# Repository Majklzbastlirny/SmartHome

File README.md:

# SmartHome
My smarthome ecosystem

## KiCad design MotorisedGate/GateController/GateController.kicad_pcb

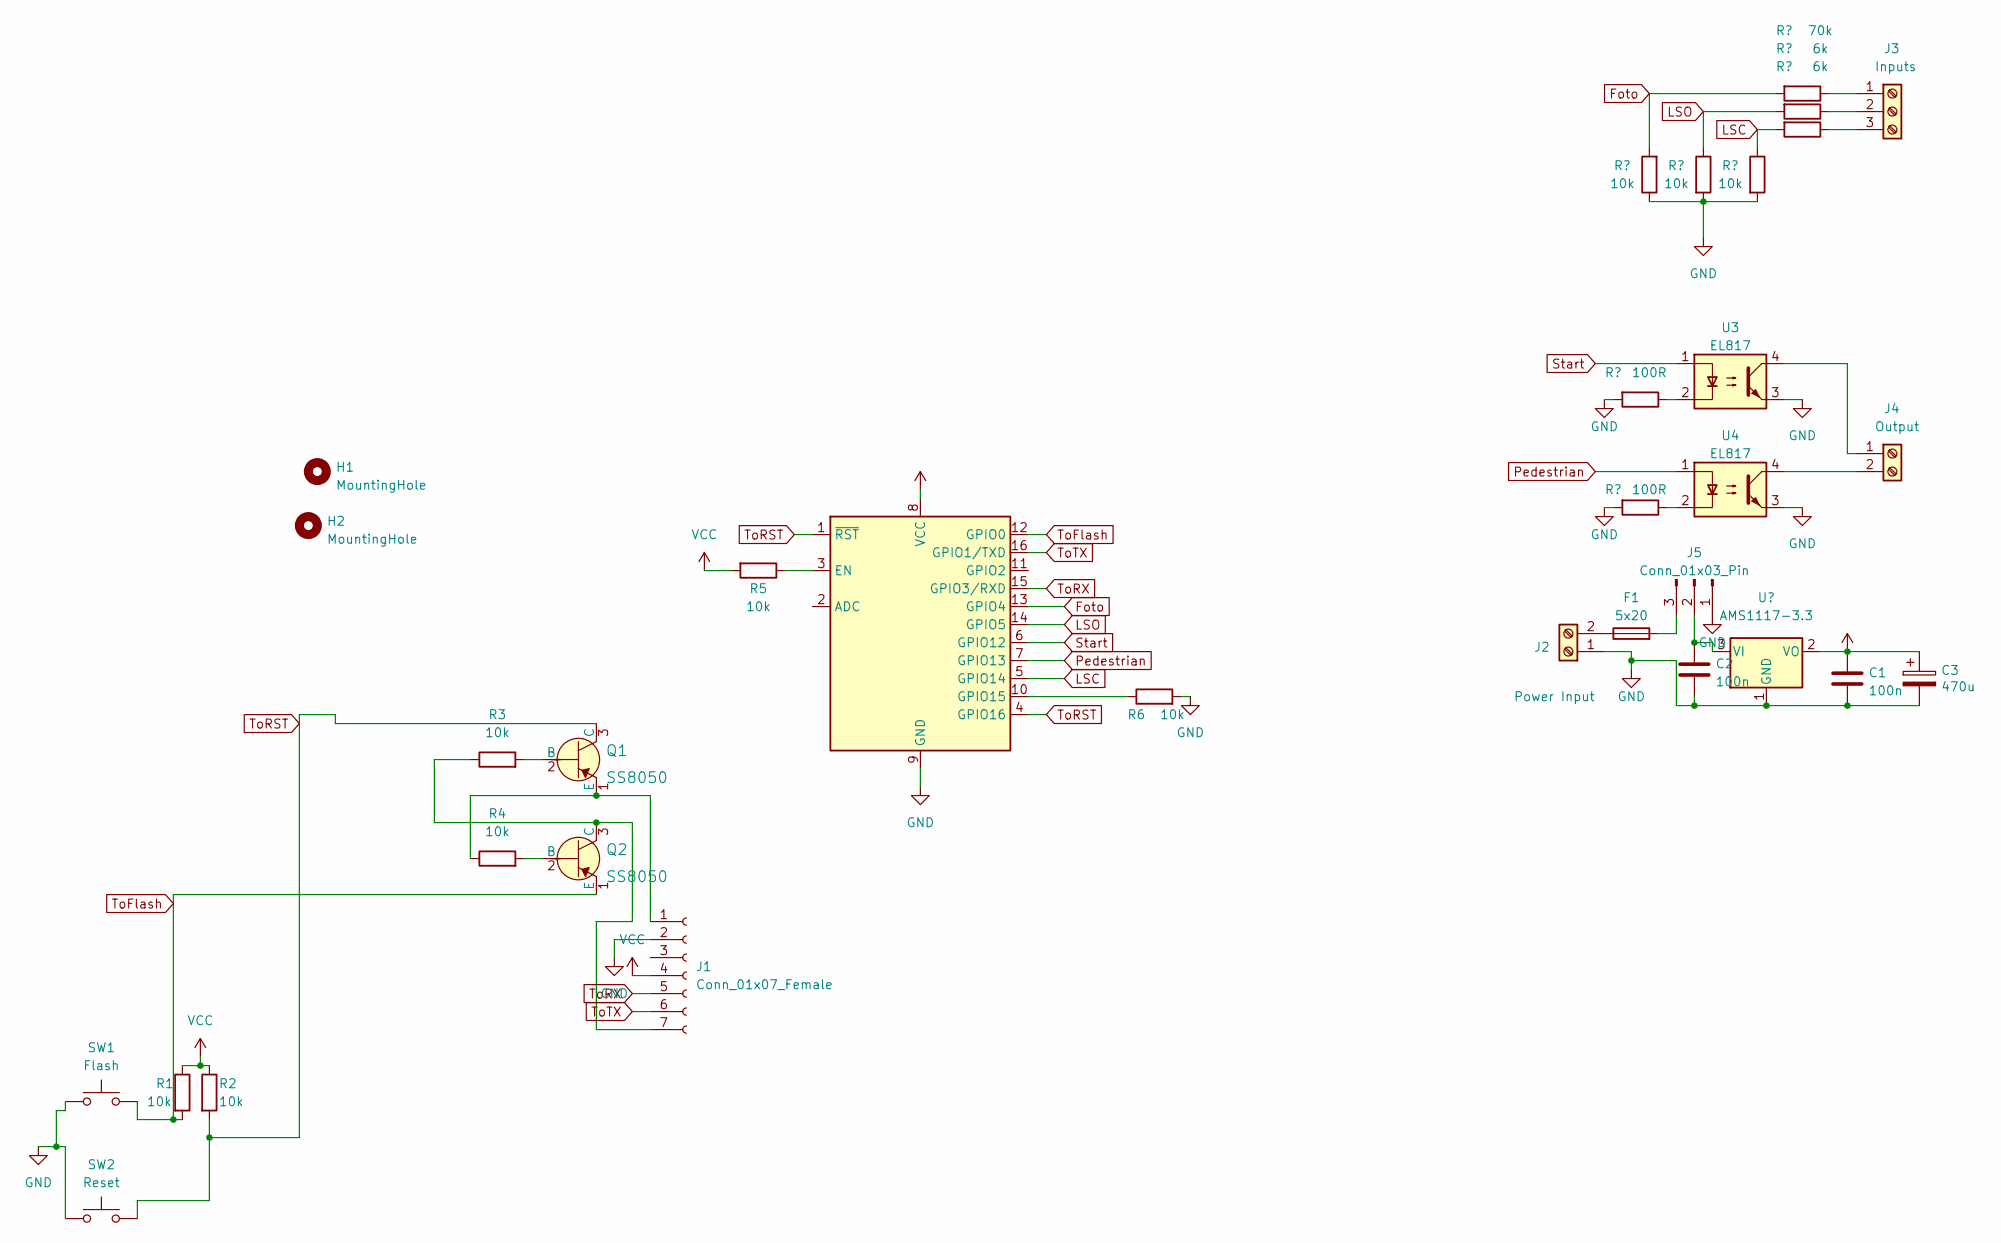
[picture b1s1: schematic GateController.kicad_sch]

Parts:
C1, C2: 100n; C_Disc_D4.3mm_W1.9mm_P5.00mm
C3: 470u; CP_Radial_D8.0mm_P3.80mm
F1: 5x20; Fuseholder_Cylinder-5x20mm_Stelvio-Kontek_PTF76_Horizontal_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
H1, H2: MountingHole; MountingHole_3mm
J1: Conn_01x07_Female; PinHeader_1x07_P2.54mm_Vertical
J2: Power Input; TerminalBlock_Altech_AK300-2_P5.00mm
J3: Inputs; TerminalBlock_Altech_AK300-3_P5.00mm
J4: Output; TerminalBlock_Altech_AK300-2_P5.00mm
J5: Conn_01x03_Pin; PinHeader_1x03_P2.54mm_Vertical
Q1, Q2: SS8050; TO-92L_Inline_Wide; MPN 2N2222; Digi-Key_PN 2N2222CS-ND
R1, R2, R3, R4, R5, R6, R9, R10, R11: 10k; R_Axial_DIN0207_L6.3mm_D2.5mm_P10.16mm_Horizontal
R7, R8: 100R; R_Axial_DIN0207_L6.3mm_D2.5mm_P10.16mm_Horizontal
R12: 70k; R_Axial_DIN0207_L6.3mm_D2.5mm_P10.16mm_Horizontal
R13, R14: 6k; R_Axial_DIN0207_L6.3mm_D2.5mm_P10.16mm_Horizontal
SW1: Flash; SW_PUSH_6mm
SW2: Reset; SW_PUSH_6mm
U1: ESP-07
U2: AMS1117-3.3; SOT-223-3_TabPin2
U3, U4: EL817; DIP-4_W7.62mm

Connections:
Foto: R9.2, R12.2, U1.13 (GPIO4)
GND: C1.2, C2.2, C3.2, J1.2, J2.1, J5.1, R6.2, R7.2, R8.2, R9.1, R10.2, R11.2, SW1.1, SW2.1, U1.9 (GND), U2.1 (GND), U3.3, U4.3
LSC: R11.1, R14.2, U1.5 (GPIO14)
LSO: R10.1, R13.2, U1.14 (GPIO5)
unnamed: J1.1, Q1.1 (E), R4.1
unnamed: J1.7, Q2.3 (C), R3.1
unnamed: F1.1, J2.2
unnamed: J3.1, R12.1
unnamed: J3.2, R13.1
unnamed: J3.3, R14.1
unnamed: J4.1, U3.4
unnamed: J4.2, U4.4
unnamed: C2.1, J5.2, U2.3 (VI)
unnamed: F1.2, J5.3
unnamed: Q1.2 (B), R3.2
unnamed: Q2.2 (B), R4.2
unnamed: R7.1, U3.2
unnamed: R8.1, U4.2
unnamed: R5.1, U1.3 (EN)
unnamed: R6.1, U1.10 (GPIO15)
Pedestrian: U1.7 (GPIO13), U4.1
Start: U1.6 (GPIO12), U3.1
ToFlash: Q2.1 (E), R1.2, SW1.2, U1.12 (GPIO0)
ToRST: Q1.3 (C), R2.2, SW2.2, U1.1 (~RST), U1.4 (GPIO16)
ToRX: J1.5, U1.15 (GPIO3/RXD)
ToTX: J1.6, U1.16 (GPIO1/TXD)
VCC: C1.1, C3.1, J1.4, R1.1, R2.1, R5.2, U1.8 (VCC), U2.2 (VO)

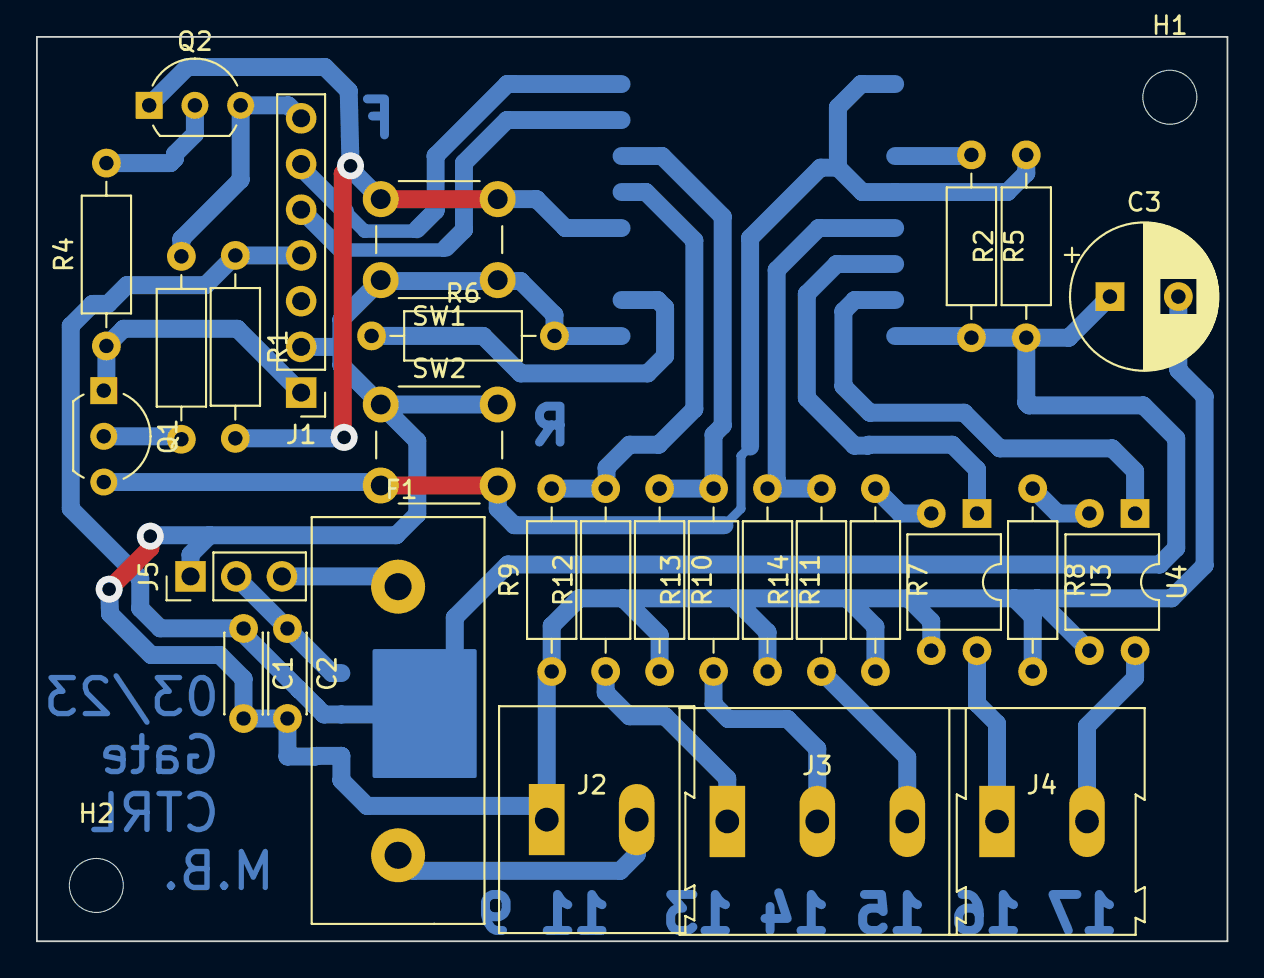
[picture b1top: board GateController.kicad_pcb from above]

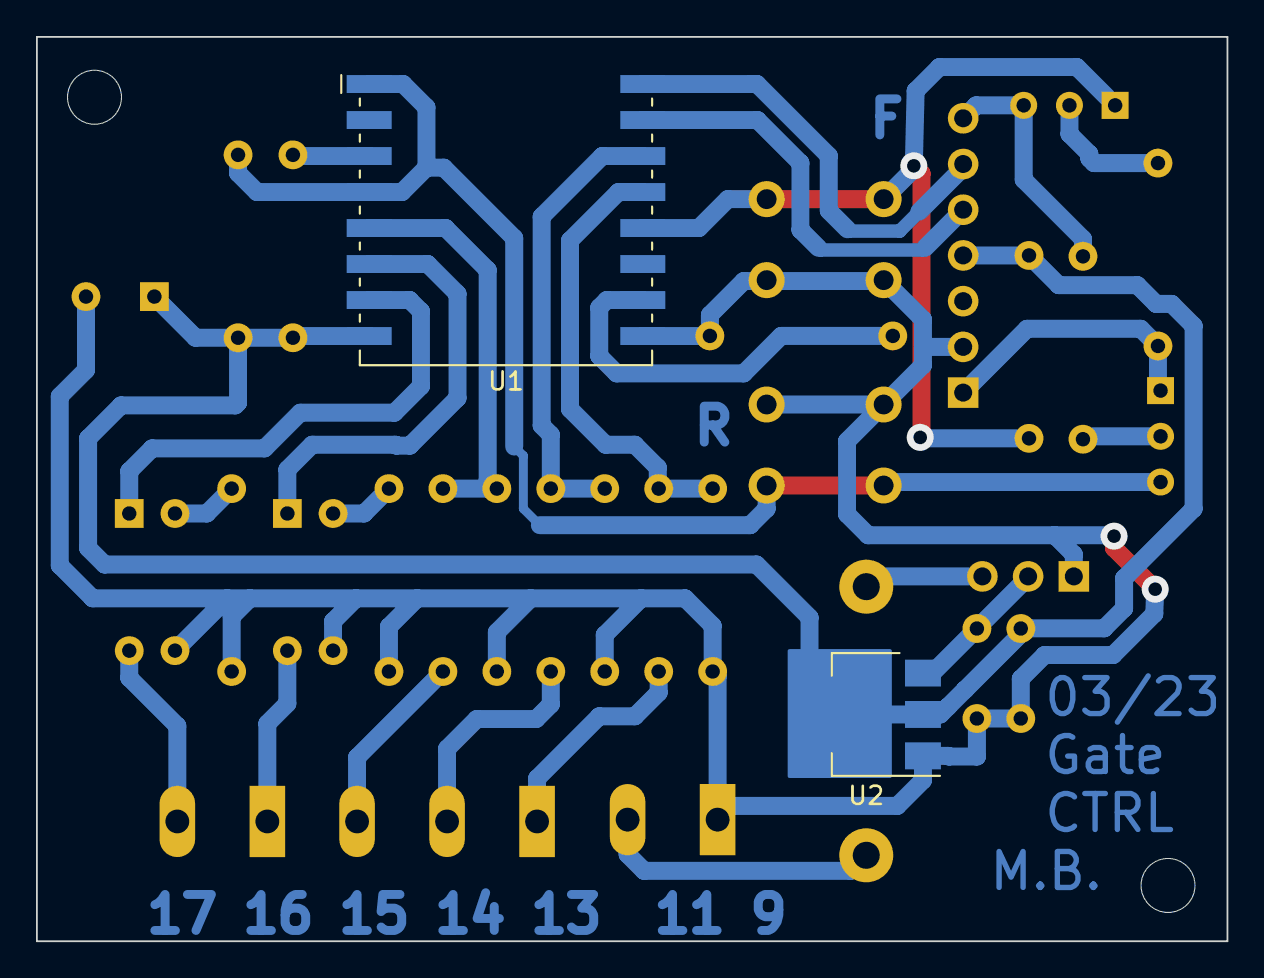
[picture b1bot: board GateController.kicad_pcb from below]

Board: 2 copper layers, 66.1 x 50.2 mm, 33 parts (2 on the bottom side), 27 nets.

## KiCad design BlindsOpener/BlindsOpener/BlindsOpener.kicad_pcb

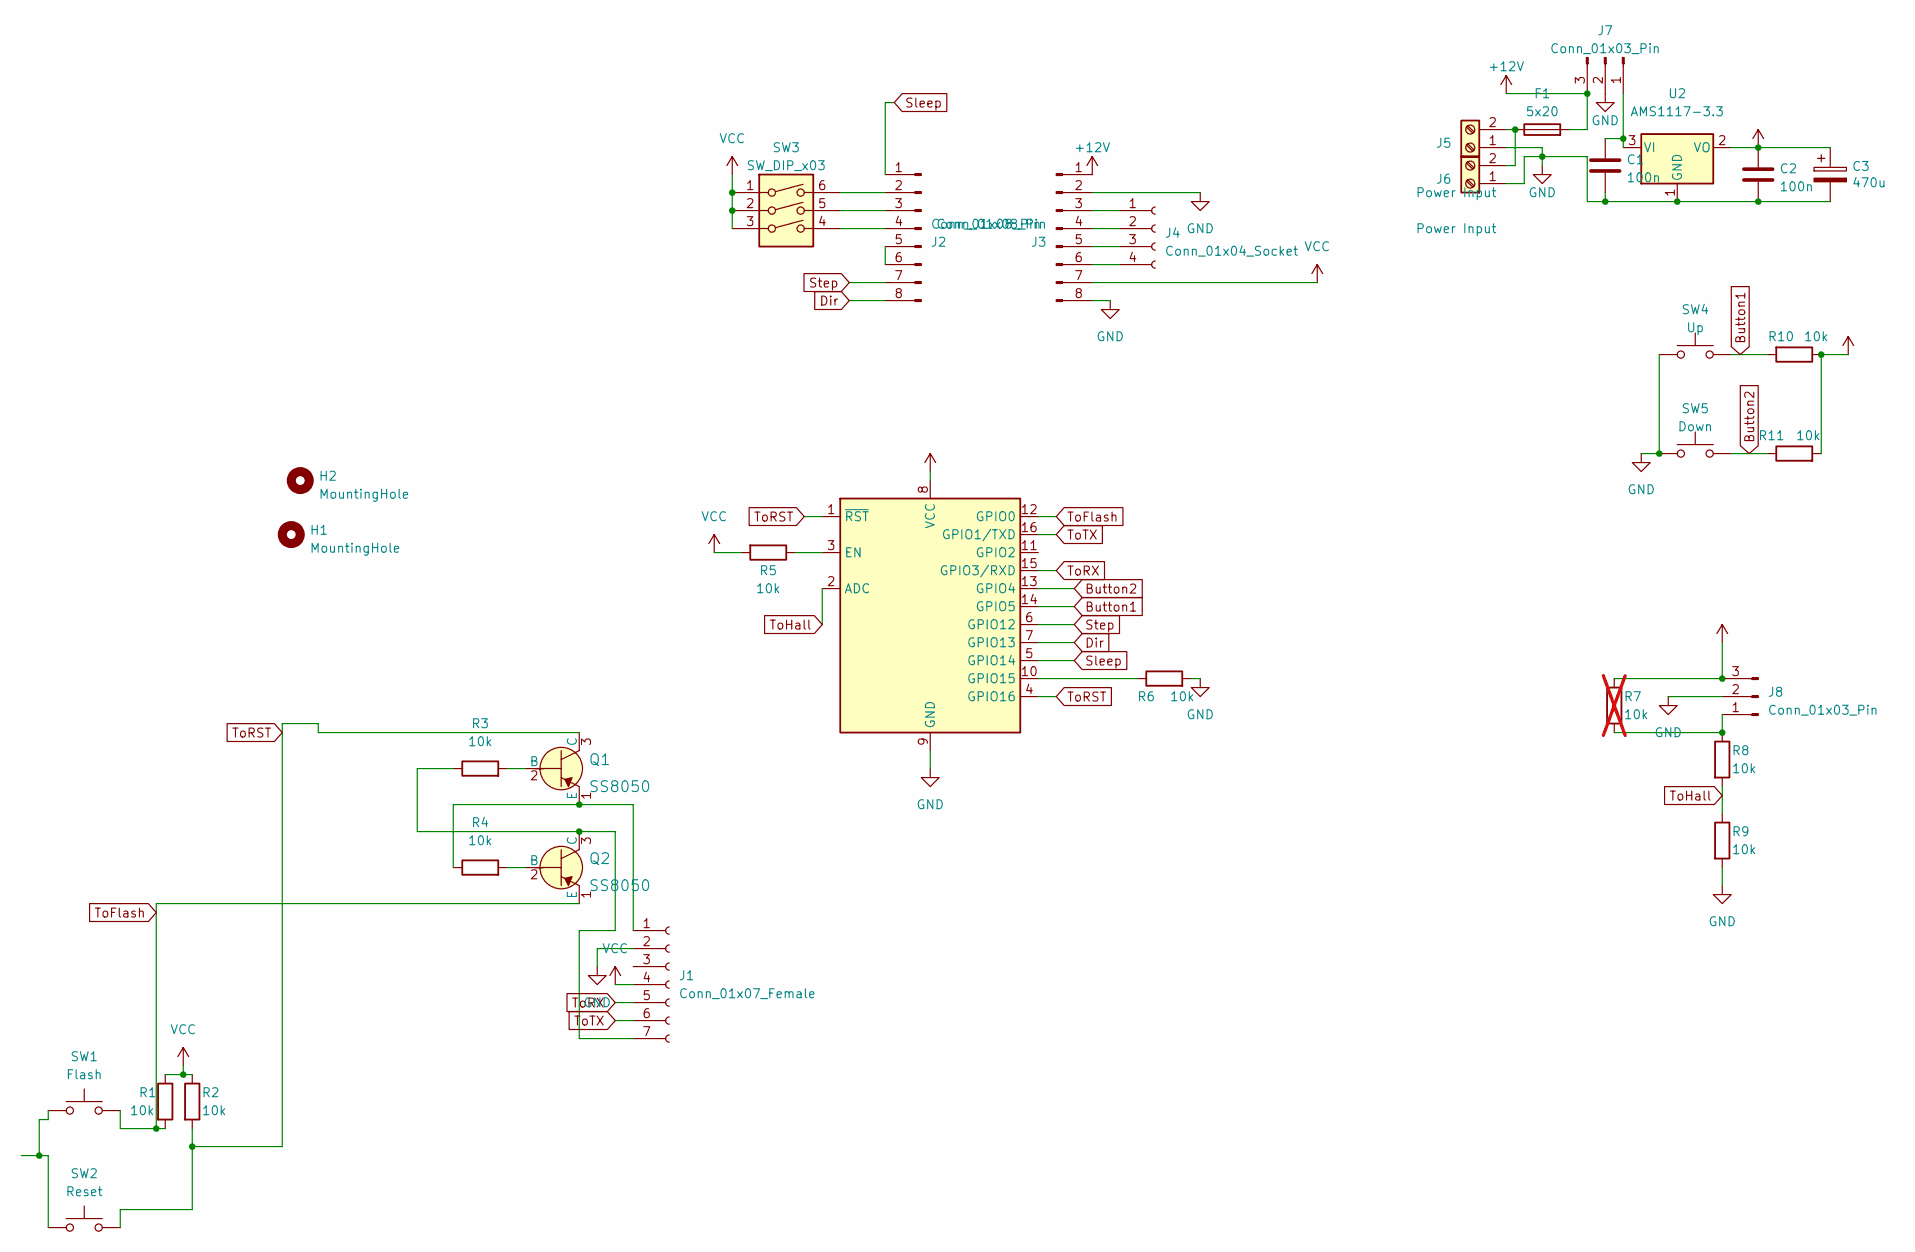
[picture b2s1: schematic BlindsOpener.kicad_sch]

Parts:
C1, C2: 100n; C_Disc_D4.3mm_W1.9mm_P5.00mm
C3: 470u; CP_Radial_D8.0mm_P3.80mm
F1: 5x20; Fuseholder_Cylinder-5x20mm_Stelvio-Kontek_PTF76_Horizontal_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
H1, H2: MountingHole; MountingHole_3mm
J1: Conn_01x07_Female; PinHeader_1x07_P2.54mm_Vertical
J2, J3: Conn_01x08_Pin; PinSocket_1x08_P2.54mm_Vertical
J4: Conn_01x04_Socket; FanPinHeader_1x04_P2.54mm_Vertical
J5, J6: Power Input; TerminalBlock_Altech_AK300-2_P5.00mm
J7, J8: Conn_01x03_Pin; PinHeader_1x03_P2.54mm_Vertical
Q1, Q2: SS8050; TO-92L_Inline_Wide; MPN 2N2222; Digi-Key_PN 2N2222CS-ND
R1, R2, R3, R4, R5, R6, R8, R9, R10, R11: 10k; R_Axial_DIN0207_L6.3mm_D2.5mm_P10.16mm_Horizontal
R7: 10k; R_Axial_DIN0207_L6.3mm_D2.5mm_P10.16mm_Horizontal; not fitted
SW1: Flash; SW_PUSH_6mm
SW2: Reset; SW_PUSH_6mm
SW3: SW_DIP_x03; SW_DIP_SPSTx03_Slide_6.7x9.18mm_W7.62mm_P2.54mm_LowProfile
SW4: Up; SW_PUSH_6mm
SW5: Down; SW_PUSH_6mm
U1: ESP-07
U2: AMS1117-3.3; SOT-223-3_TabPin2

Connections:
+12V: F1.2, J3.1, J7.3
Button1: R10.2, SW4.2, U1.14 (GPIO5)
Button2: R11.1, SW5.2, U1.13 (GPIO4)
Dir: J2.8, U1.7 (GPIO13)
GND: C1.2, C2.2, C3.2, J1.2, J3.2, J3.8, J5.1, J6.1, J7.2, J8.2, R6.2, R9.2, SW4.1, SW5.1, U1.9 (GND), U2.1 (GND)
unnamed: J1.1, Q1.1 (E), R4.1
unnamed: J1.7, Q2.3 (C), R3.1
unnamed: J2.2, SW3.6
unnamed: J2.3, SW3.5
unnamed: J2.4, SW3.4
unnamed: J2.5, J2.6
unnamed: J3.3, J4.1
unnamed: J3.4, J4.2
unnamed: J3.5, J4.3
unnamed: J3.6, J4.4
unnamed: F1.1, J5.2, J6.2
unnamed: C1.1, J7.1, U2.3 (VI)
unnamed: J8.1, R7.2, R8.1
unnamed: Q1.2 (B), R3.2
unnamed: Q2.2 (B), R4.2
unnamed: SW1.1, SW2.1
unnamed: R5.1, U1.3 (EN)
unnamed: R6.1, U1.10 (GPIO15)
Sleep: J2.1, U1.5 (GPIO14)
Step: J2.7, U1.6 (GPIO12)
ToFlash: Q2.1 (E), R1.2, SW1.2, U1.12 (GPIO0)
ToHall: R8.2, R9.1, U1.2 (ADC)
ToRST: Q1.3 (C), R2.2, SW2.2, U1.1 (~RST), U1.4 (GPIO16)
ToRX: J1.5, U1.15 (GPIO3/RXD)
ToTX: J1.6, U1.16 (GPIO1/TXD)
VCC: C2.1, C3.1, J1.4, J3.7, J8.3, R1.1, R2.1, R5.2, R7.1, R10.1, R11.2, SW3.1, SW3.2, SW3.3, U1.8 (VCC), U2.2 (VO)

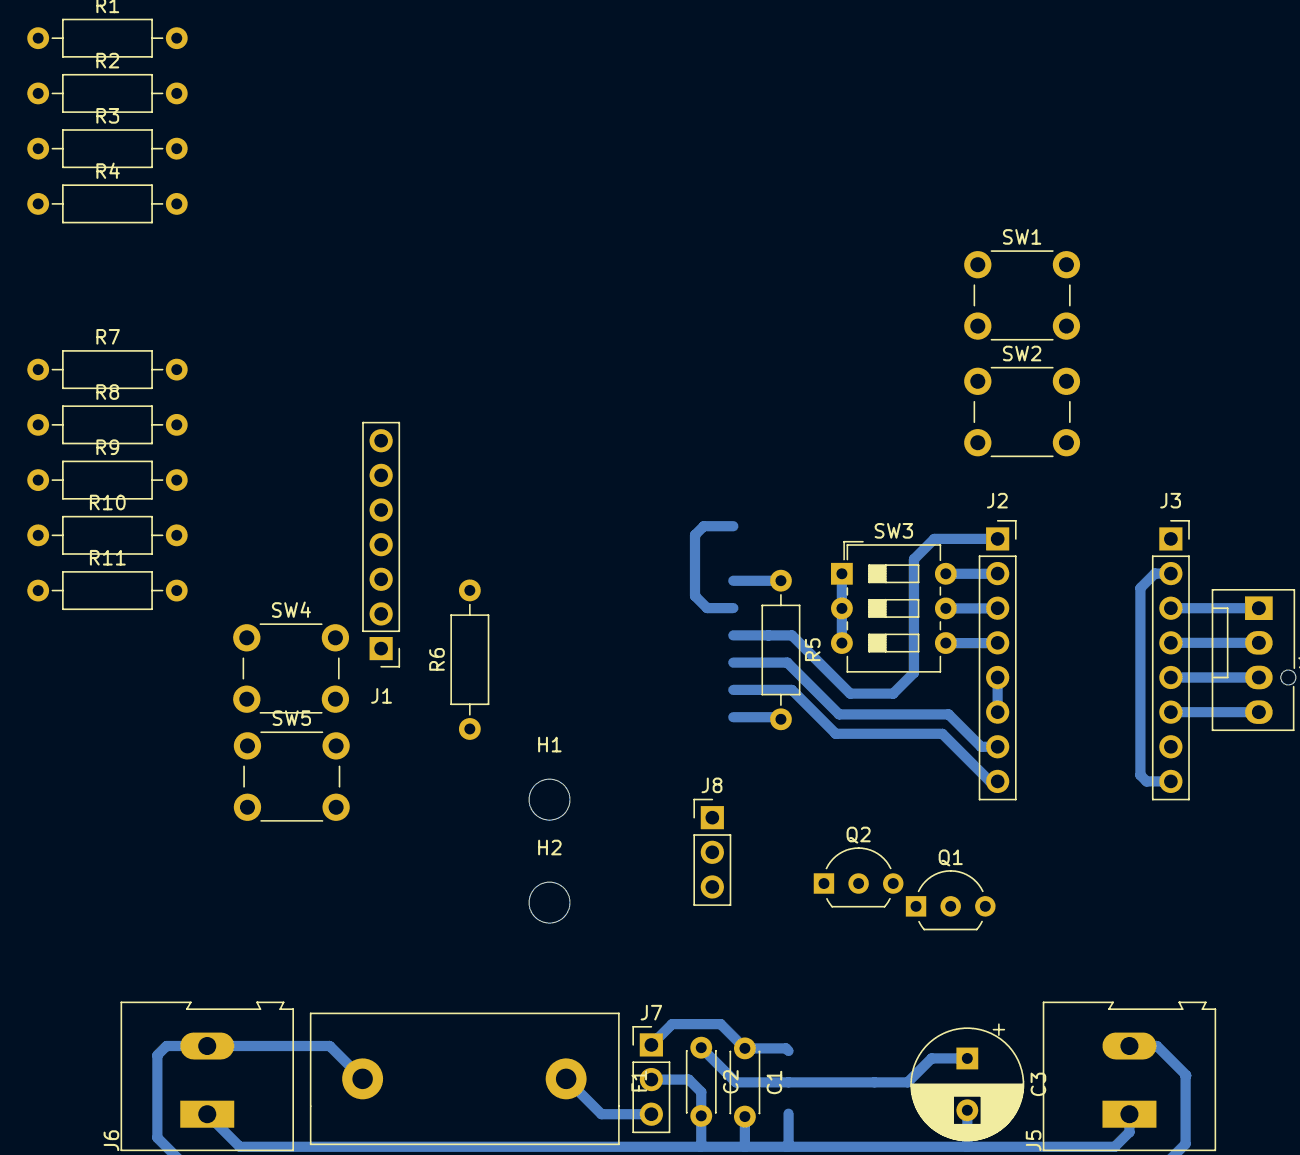
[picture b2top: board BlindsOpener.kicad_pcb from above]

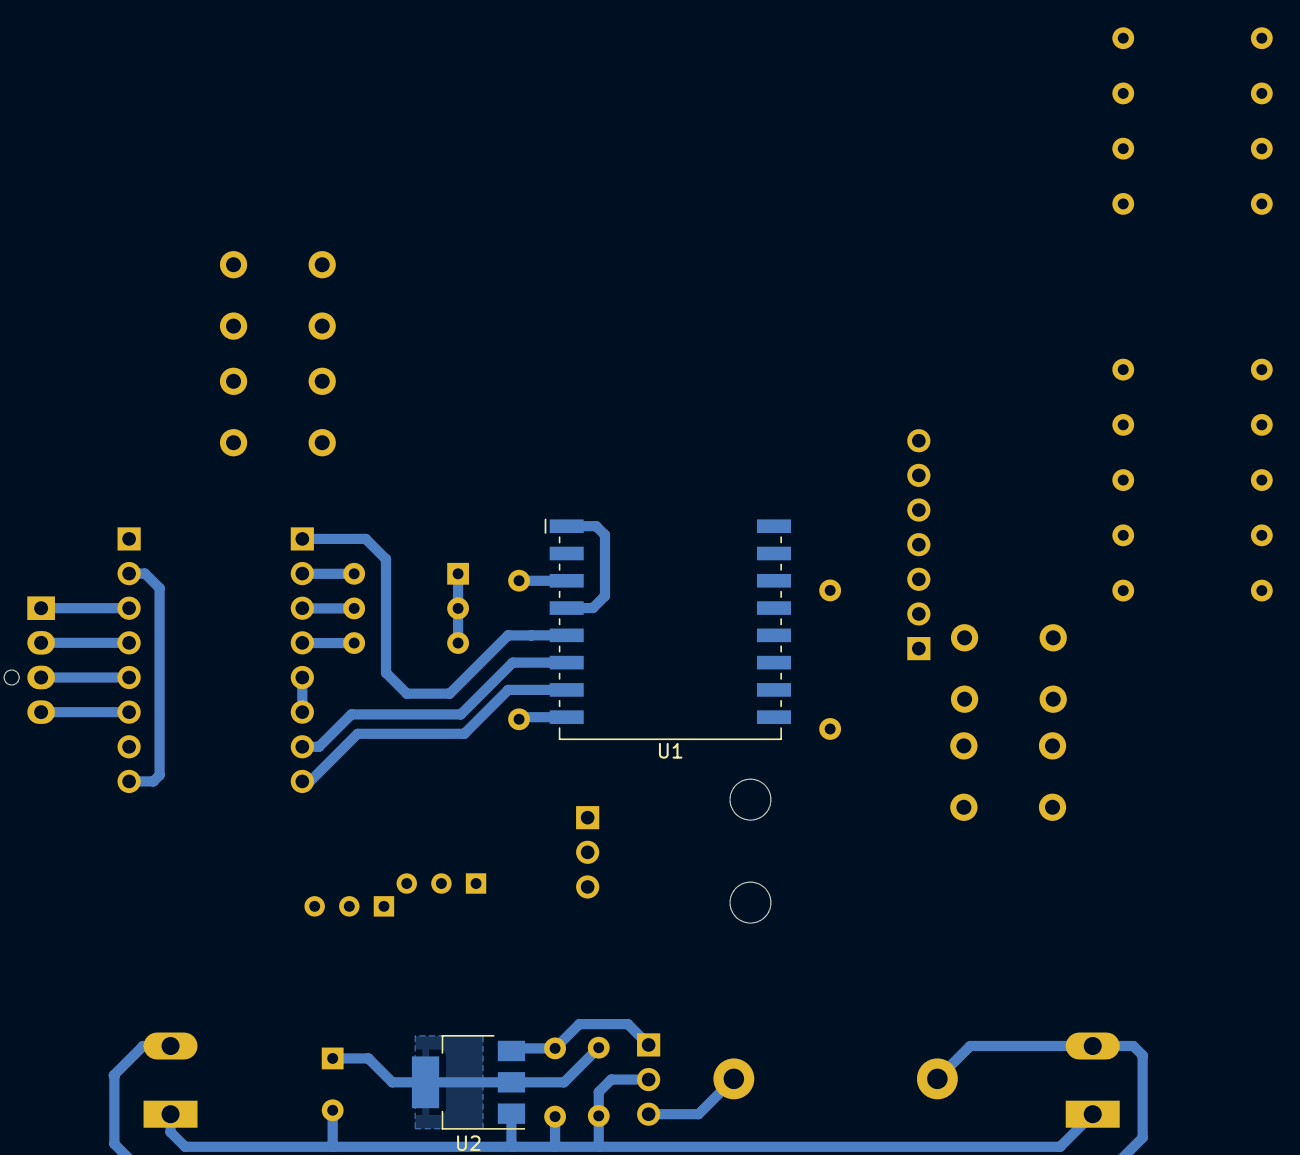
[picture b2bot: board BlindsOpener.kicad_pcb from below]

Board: 2 copper layers, 34 parts (2 on the bottom side), 31 nets.

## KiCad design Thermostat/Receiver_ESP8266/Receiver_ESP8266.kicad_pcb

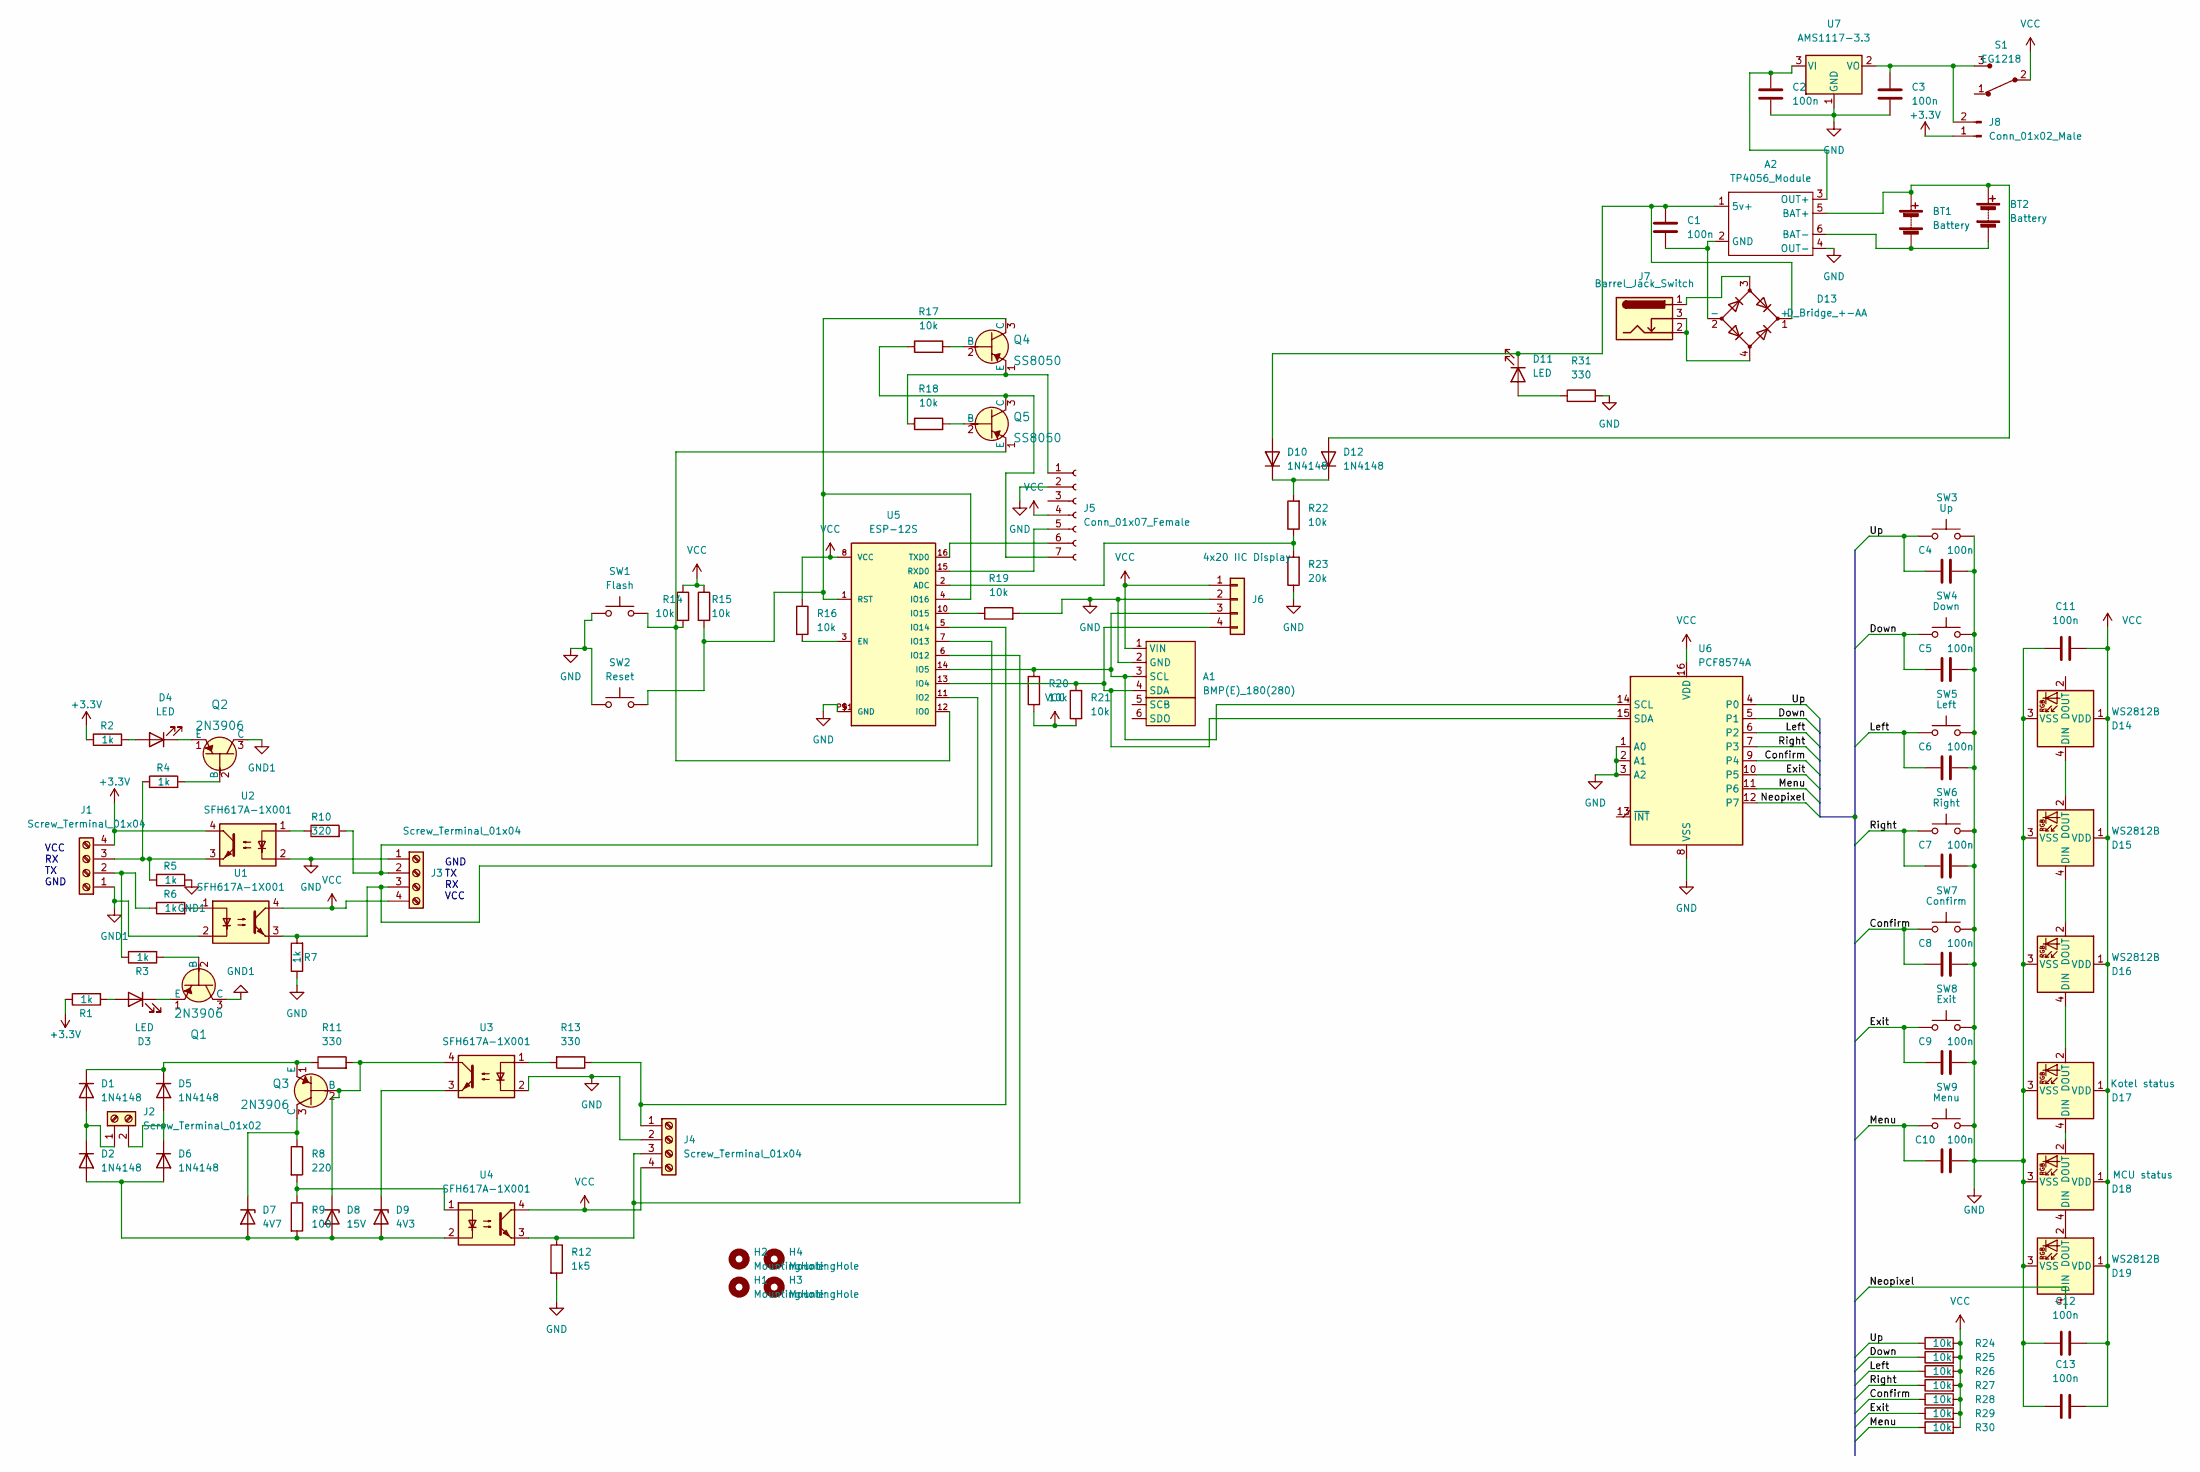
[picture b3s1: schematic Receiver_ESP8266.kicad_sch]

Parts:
A1: BMP(E)_180(280); PinHeader_1x06_P2.54mm_Vertical
A2: TP4056_Module; TP4056-18650
BT1, BT2: Battery; BatteryHolder_MPD_BH-18650-PC2
C1, C2, C3, C4, C5, C6, C7, C8, C9, C10, C11, C12, C13: 100n; C_Disc_D7.0mm_W2.5mm_P5.00mm
D1, D2, D5, D6, D10, D12: 1N4148; D_DO-35_SOD27_P7.62mm_Horizontal
D3, D4, D11: LED; LED_D5.0mm_Clear
D7: 4V7; D_A-405_P10.16mm_Horizontal
D8: 15V; D_A-405_P10.16mm_Horizontal
D9: 4V3; D_A-405_P10.16mm_Horizontal
D13: D_Bridge_+-AA; Diode_Bridge_DIP-4_W7.62mm_P5.08mm
D14, D15, D16, D19: WS2812B; LED_WS2812B_PLCC4_5.0x5.0mm_P3.2mm
D17: Kotel status; LED_WS2812B_PLCC4_5.0x5.0mm_P3.2mm
D18: MCU status; LED_WS2812B_PLCC4_5.0x5.0mm_P3.2mm
H1, H2, H3, H4: MountingHole; MountingHole_3.2mm_M3_DIN965_Pad_TopBottom
J1: Screw_Terminal_01x04; TerminalBlock_Altech_AK300-4_P5.00mm
J2: Screw_Terminal_01x02; TerminalBlock_Altech_AK300-2_P5.00mm
J3, J4: Screw_Terminal_01x04; PinHeader_1x04_P2.54mm_Vertical
J5: Conn_01x07_Female; PinHeader_1x07_P2.54mm_Vertical
J6: 4x20 IIC Display; PinHeader_1x04_P2.54mm_Vertical
J7: Barrel_Jack_Switch; BarrelJack_Horizontal
J8: Conn_01x02_Male; PinHeader_1x02_P2.54mm_Vertical
Q1, Q2, Q3: 2N3906; TO-92L_Inline_Wide; MPN 2N2222; Digi-Key_PN 2N2222CS-ND
Q4, Q5: SS8050; TO-92L_Inline_Wide; MPN 2N2222; Digi-Key_PN 2N2222CS-ND
R1, R2, R3, R4, R5, R6, R7: 1k; R_Axial_DIN0411_L9.9mm_D3.6mm_P5.08mm_Vertical
R8: 220; R_Axial_DIN0411_L9.9mm_D3.6mm_P5.08mm_Vertical
R9: 100; R_Axial_DIN0411_L9.9mm_D3.6mm_P5.08mm_Vertical
R10: 320; R_Axial_DIN0411_L9.9mm_D3.6mm_P5.08mm_Vertical
R11, R13, R31: 330; R_Axial_DIN0411_L9.9mm_D3.6mm_P5.08mm_Vertical
R12: 1k5; R_Axial_DIN0411_L9.9mm_D3.6mm_P5.08mm_Vertical
R14, R15, R16, R17, R18, R19, R20, R21, R22, R24, R25, R26, R27, R28, R29, R30: 10k; R_Axial_DIN0411_L9.9mm_D3.6mm_P5.08mm_Vertical
R23: 20k; R_Axial_DIN0411_L9.9mm_D3.6mm_P5.08mm_Vertical
S1: EG1218; SW_CuK_OS102011MA1QN1_SPDT_Angled; MPN EG1218; Digi-Key_PN EG1903-ND
SW1: Flash; SW_PUSH_6mm
SW2: Reset; SW_PUSH_6mm
SW3: Up; SW_PUSH_6mm
SW4: Down; SW_PUSH_6mm
SW5: Left; SW_PUSH_6mm
SW6: Right; SW_PUSH_6mm
SW7: Confirm; SW_PUSH_6mm
SW8: Exit; SW_PUSH_6mm
SW9: Menu; SW_PUSH_6mm
U1, U2, U3, U4: SFH617A-1X001; DIP-4_W7.62mm
U5: ESP-12S; ESP-07
U6: PCF8574A; DIP-16_W7.62mm_Socket_LongPads
U7: AMS1117-3.3; SOT-223-3_TabPin2

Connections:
+3V3: J1.4, J8.1, R1.1, R2.1, U2.4
/Confirm: C8.1, R28.1, SW7.1, U6.9 (P4)
/Down: C5.1, R25.1, SW4.1, U6.5 (P1)
/Exit: C9.1, R29.1, SW8.1, U6.10 (P5)
/Left: C6.1, R26.1, SW5.1, U6.6 (P2)
/Menu: C10.1, R30.1, SW9.1, U6.11 (P6)
/Neopixel: D19.4 (DIN), U6.12 (P7)
/Right: C7.1, R27.1, SW6.1, U6.7 (P3)
/Up: C4.1, R24.1, SW3.1, U6.4 (P0)
GND: A1.2 (GND), A2.4 (OUT-), C2.2, C3.2, C4.2, C5.2, C6.2, C7.2, C8.2, C9.2, C10.2, C11.1, C12.1, C13.1, D14.3 (VSS), D15.3 (VSS), D16.3 (VSS), D17.3 (VSS), D18.3 (VSS), D19.3 (VSS), J3.1, J4.2, J5.2, J6.2, R7.1, R12.2, R19.2, R23.1, R31.2, SW1.1, SW2.1, SW3.2, SW4.2, SW5.2, SW6.2, SW7.2, SW8.2, SW9.2, U2.2, U3.2, U5.9 (GND), U5.P$1 (GND), U6.1 (A0), U6.2 (A1), U6.3 (A2), U6.8 (VSS), U7.1 (GND)
GND1: J1.1, Q1.3 (C), Q2.3 (C), R5.2, U1.2
unnamed: A1.3 (SCL), J6.3, R20.2, U5.14 (IO5), U6.14 (SCL)
unnamed: A1.4 (SDA), J6.4, R21.2, U5.13 (IO4), U6.15 (SDA)
unnamed: A2.1 (5v+), C1.1, D10.2 (A), D11.1 (K), D13.1 (+)
unnamed: A2.2 (GND), C1.2, D13.2 (-)
unnamed: A2.3 (OUT+), C2.1, U7.3 (VI)
unnamed: A2.5 (BAT+), BT1.1 (+), BT2.1 (+), D12.2 (A)
unnamed: A2.6 (BAT-), BT1.2 (-), BT2.2 (-)
unnamed: C3.1, J8.2, S1.3, U7.2 (VO)
unnamed: D1.1 (K), D5.1 (K), Q3.1 (E), R11.1
unnamed: D1.2 (A), D2.1 (K), J2.1
unnamed: D2.2 (A), D6.2 (A), D7.2 (A), D8.2 (A), D9.2 (A), R9.2, U4.2
unnamed: D3.1 (K), Q1.1 (E)
unnamed: D3.2 (A), R1.2
unnamed: D4.1 (K), Q2.1 (E)
unnamed: D4.2 (A), R2.2
unnamed: D5.2 (A), D6.1 (K), J2.2
unnamed: D7.1 (K), Q3.3 (C), R8.1
unnamed: D8.1 (K), Q3.2 (B), R11.2, U3.4
unnamed: D9.1 (K), U3.3
unnamed: D10.1 (K), D12.1 (K), R22.2
unnamed: D11.2 (A), R31.1
unnamed: D13.3, J7.1
unnamed: D13.4, J7.2, J7.3
unnamed: D14.4 (DIN), D15.2 (DOUT)
unnamed: D15.4 (DIN), D16.2 (DOUT)
unnamed: D16.4 (DIN), D17.2 (DOUT)
unnamed: D17.4 (DIN), D18.2 (DOUT)
unnamed: D18.4 (DIN), D19.2 (DOUT)
unnamed: J1.2, R3.1, R6.1
unnamed: J1.3, R4.1, R5.1, U2.3
unnamed: J3.2, R10.2, U5.11 (IO2)
unnamed: J3.3, R7.2, U1.3, U5.7 (IO13)
unnamed: J4.1, R13.1, U5.5 (IO14)
unnamed: J4.3, R12.1, U4.3, U5.6 (IO12)
unnamed: J5.1, Q4.1 (E), R18.1
unnamed: J5.5, U5.15 (RXD0)
unnamed: J5.6, U5.16 (TXD0)
unnamed: J5.7, Q5.3 (C), R17.1
unnamed: Q1.2 (B), R3.2
unnamed: Q2.2 (B), R4.2
unnamed: Q4.2 (B), R17.2
unnamed: Q4.3 (C), R15.2, SW2.2, U5.1 (RST), U5.4 (IO16)
unnamed: Q5.1 (E), R14.2, SW1.2, U5.12 (IO0)
unnamed: Q5.2 (B), R18.2
unnamed: R6.2, U1.1
unnamed: R8.2, R9.1, U4.1
unnamed: R10.1, U2.1
unnamed: R13.2, U3.1
unnamed: R16.2, U5.3 (EN)
unnamed: R19.1, U5.10 (IO15)
unnamed: R22.1, R23.2, U5.2 (ADC)
VCC: A1.1 (VIN), C11.2, C12.2, C13.2, D14.1 (VDD), D15.1 (VDD), D16.1 (VDD), D17.1 (VDD), D18.1 (VDD), D19.1 (VDD), J3.4, J4.4, J5.4, J6.1, R14.1, R15.1, R16.1, R20.1, R21.1, R24.2, R25.2, R26.2, R27.2, R28.2, R29.2, R30.2, S1.2, U1.4, U4.4, U5.8 (VCC), U6.16 (VDD)

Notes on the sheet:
VCC RX TX GND
GND TX RX VCC

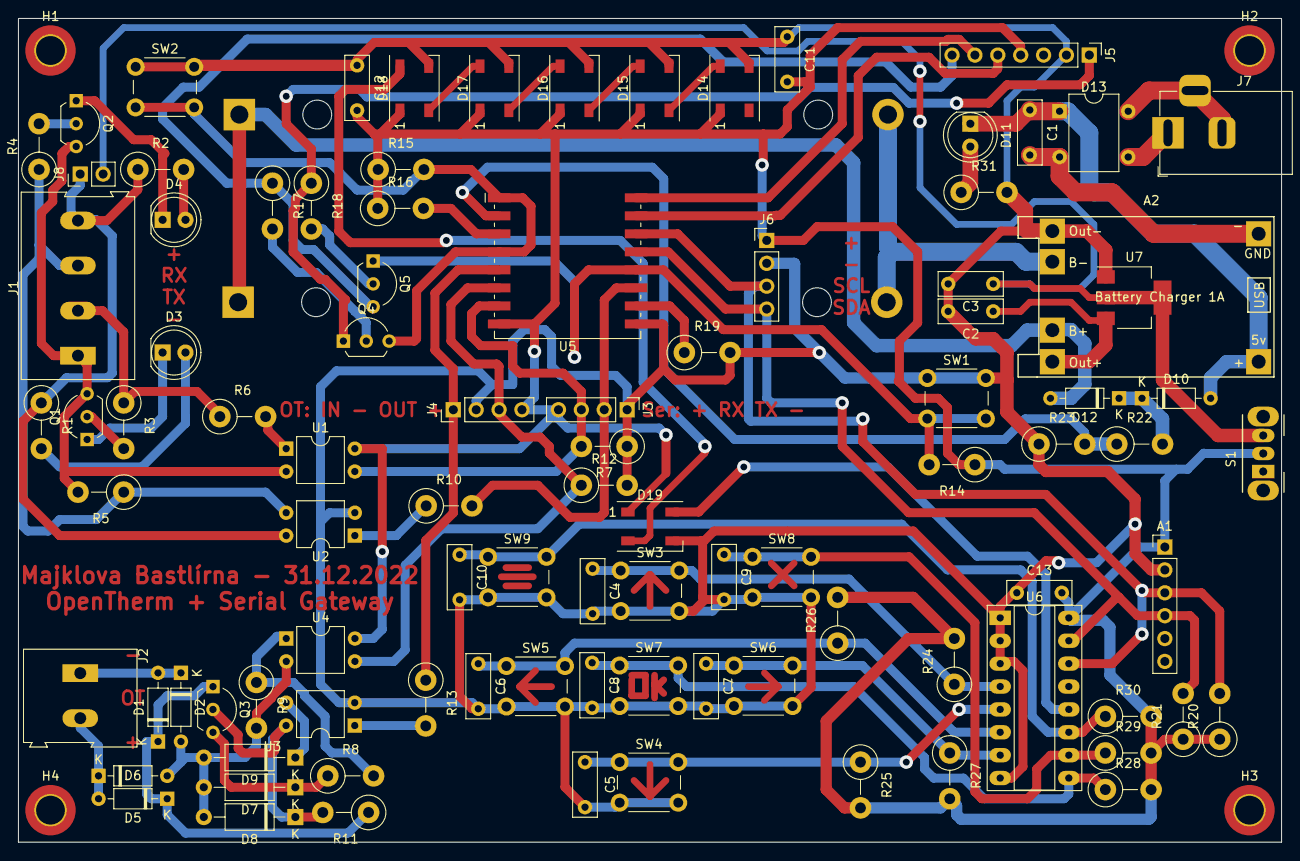
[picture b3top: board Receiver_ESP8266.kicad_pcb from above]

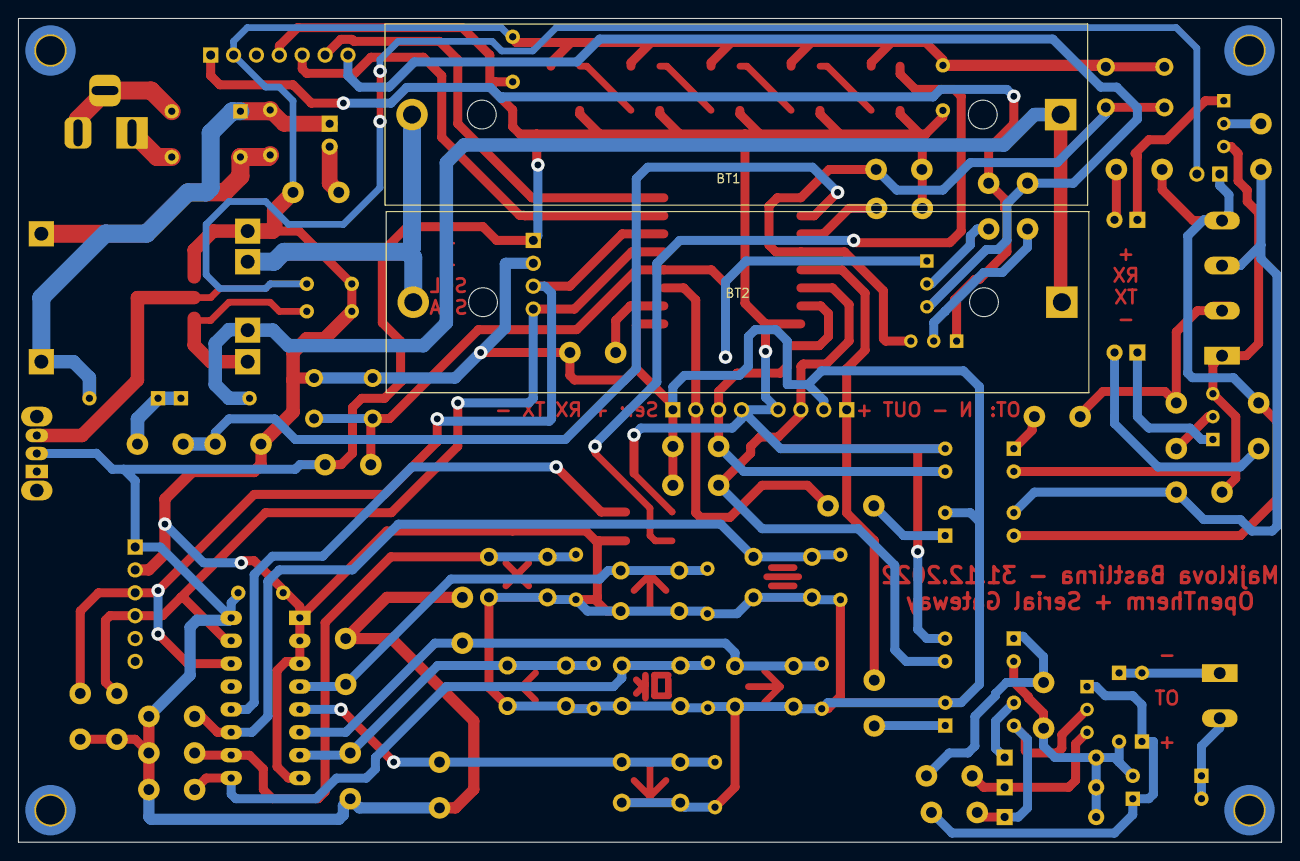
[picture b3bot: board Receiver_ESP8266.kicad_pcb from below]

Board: 2 copper layers, 140.2 x 91.4 mm, 101 parts (2 on the bottom side), 63 nets.
